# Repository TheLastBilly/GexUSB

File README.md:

# GexUSB
A remake of the USB Gecko using a Raspberry PI PICO

# Credits
- [Yet another USB Gecko clone](https://www.gc-forever.com/forums/viewtopic.php?t=3089)
    - VHDL used as a guide
    - Kicad symbols and footprint for GameCube MEMCARD
- [mcu-starter-projects](https://github.com/ataradov/mcu-starter-projects)
    - Linker script and initial Makefile
    - [tools/bin2uf2](tools/bin2uf2.c)
- [KiCad-RP-Pico](https://github.com/ncarandini/KiCad-RP-Pico)
    - Kicad symbol and footprint for Raspberry PI PICO

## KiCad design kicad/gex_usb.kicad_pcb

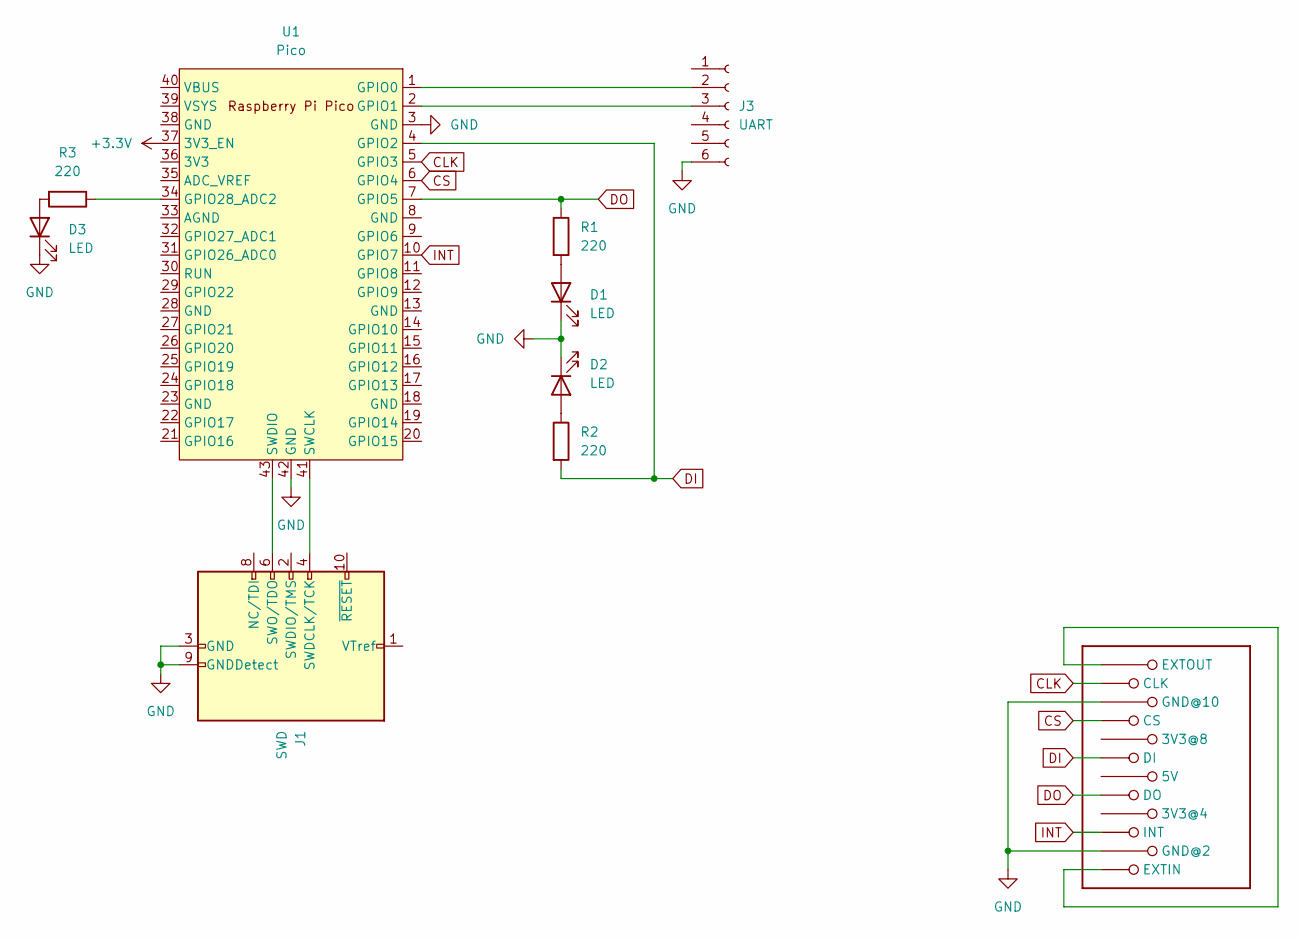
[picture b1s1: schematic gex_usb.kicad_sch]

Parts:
D1, D2, D3: LED; LED_0805_2012Metric
J1: SWD; PinHeader_2x05_P2.54mm_Vertical
J2: Memcard; GC_MEMCARD
J3: UART; PinHeader_1x06_P2.54mm_Vertical
R1, R2, R3: 220; R_0805_2012Metric
U1: Pico; RPi_Pico_SMD_TH

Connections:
+3.3V: U1.37 (3V3_EN)
CLK: J2.11 (CLK), U1.5 (GPIO3)
CS: J2.9 (CS), U1.6 (GPIO4)
DI: J2.7 (DI), R2.2, U1.4 (GPIO2)
DO: J2.5 (DO), R1.1, U1.7 (GPIO5)
GND: D1.1 (K), D2.1 (K), D3.1 (K), J1.3 (GND), J1.5 (GND), J1.9 (GNDDetect), J2.2 (GND@2), J2.10 (GND@10), J3.6, U1.3 (GND), U1.42 (GND)
INT: J2.3 (INT), U1.10 (GPIO7)
unnamed: D1.2 (A), R1.2
unnamed: D2.2 (A), R2.1
unnamed: D3.2 (A), R3.2
unnamed: J1.4 (SWDCLK/TCK), U1.41 (SWCLK)
unnamed: J1.6 (SWO/TDO), U1.43 (SWDIO)
unnamed: J2.1 (EXTIN), J2.12 (EXTOUT)
unnamed: J3.2, U1.1 (GPIO0)
unnamed: J3.3, U1.2 (GPIO1)
unnamed: R3.1, U1.34 (GPIO28_ADC2)

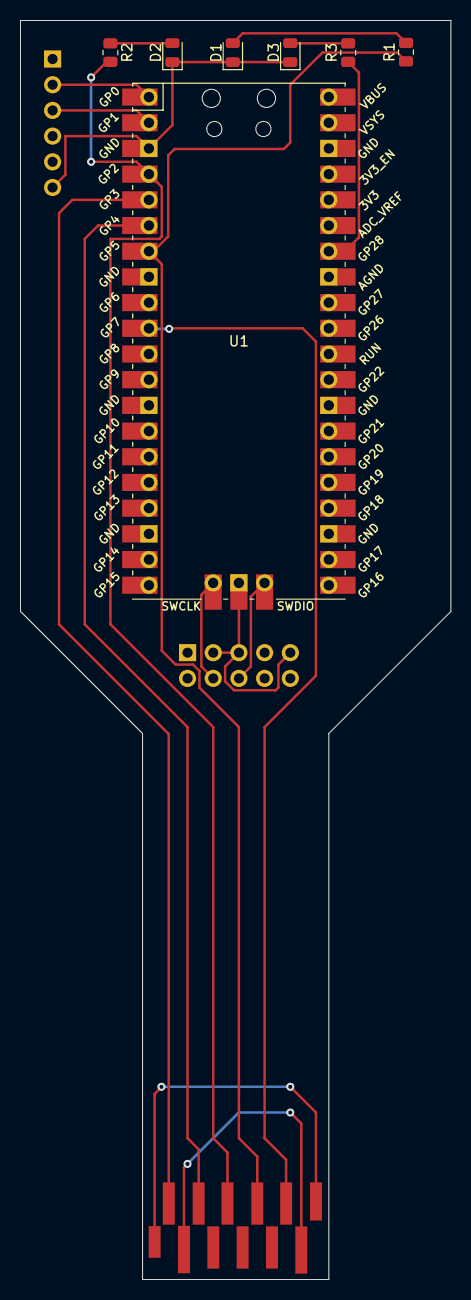
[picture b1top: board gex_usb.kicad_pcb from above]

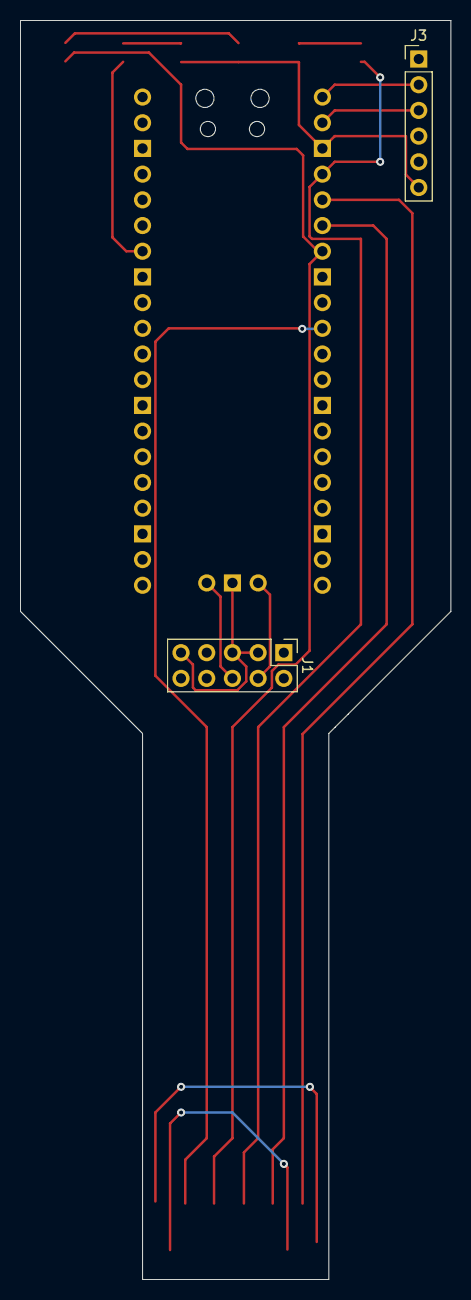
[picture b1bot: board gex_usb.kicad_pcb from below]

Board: 2 copper layers, 42.5 x 124.5 mm, 10 parts (2 on the bottom side), 15 nets.

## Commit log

2023-09-21 added kicad files
2023-09-21 added README
2023-09-21 updated credits
